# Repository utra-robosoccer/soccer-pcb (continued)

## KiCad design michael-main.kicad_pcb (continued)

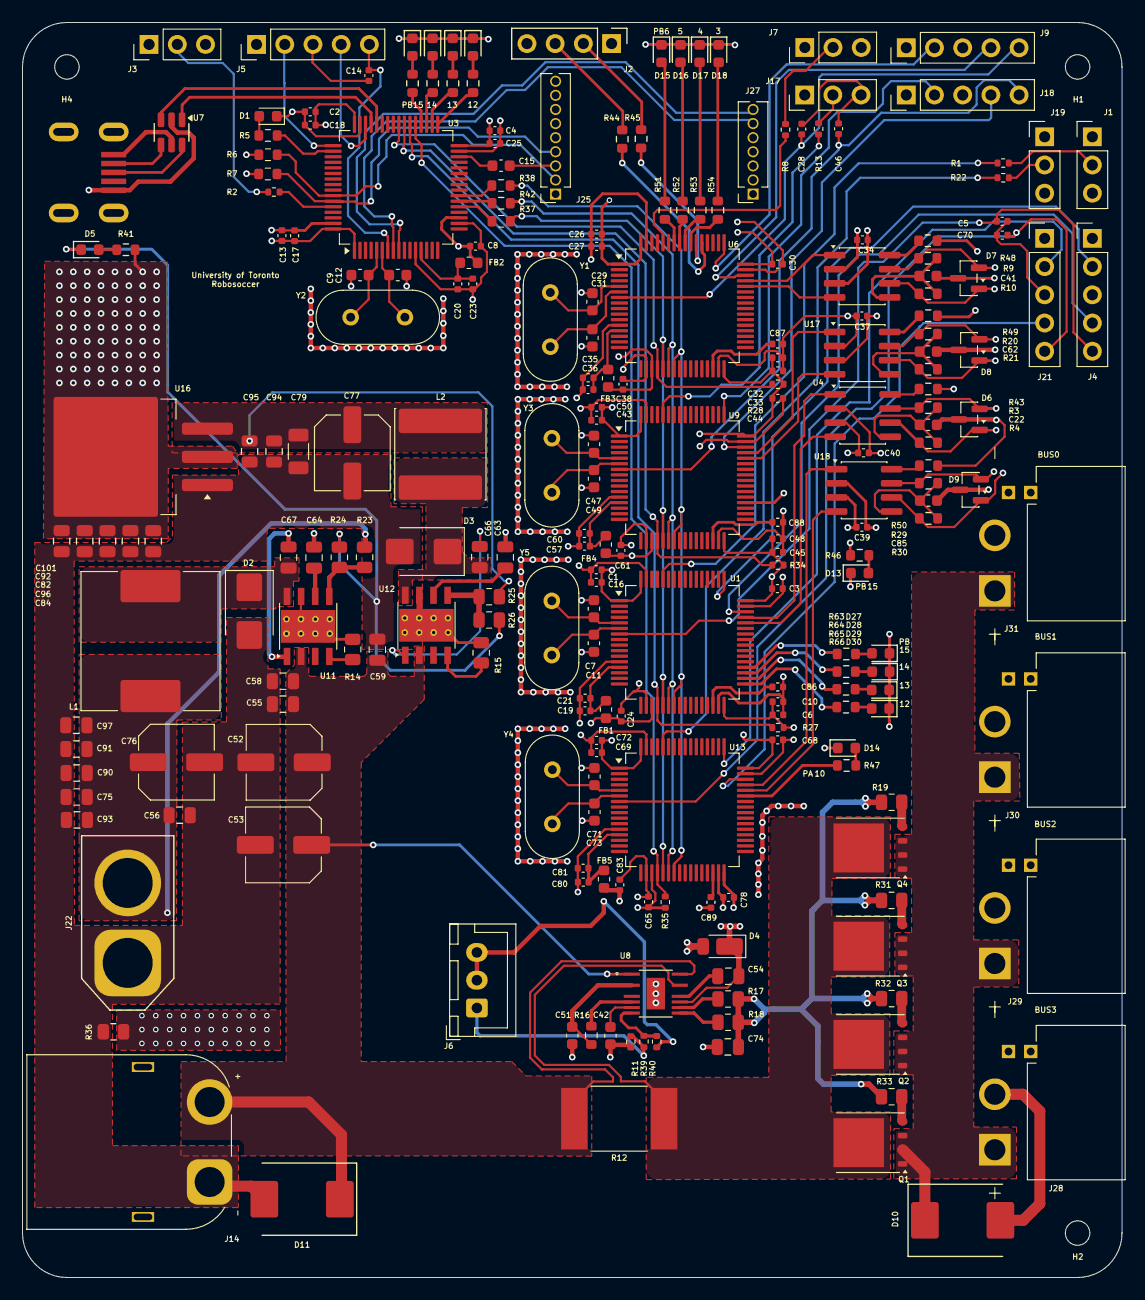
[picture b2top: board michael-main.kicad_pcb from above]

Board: 4 copper layers, 99.0 x 113.0 mm, 239 parts (0 on the bottom side), 154 nets.

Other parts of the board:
R40: 0; R_0402_1005Metric

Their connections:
+3.3V: R40.1; also elsewhere on the board
unnamed 130: R40.2; also elsewhere on the board

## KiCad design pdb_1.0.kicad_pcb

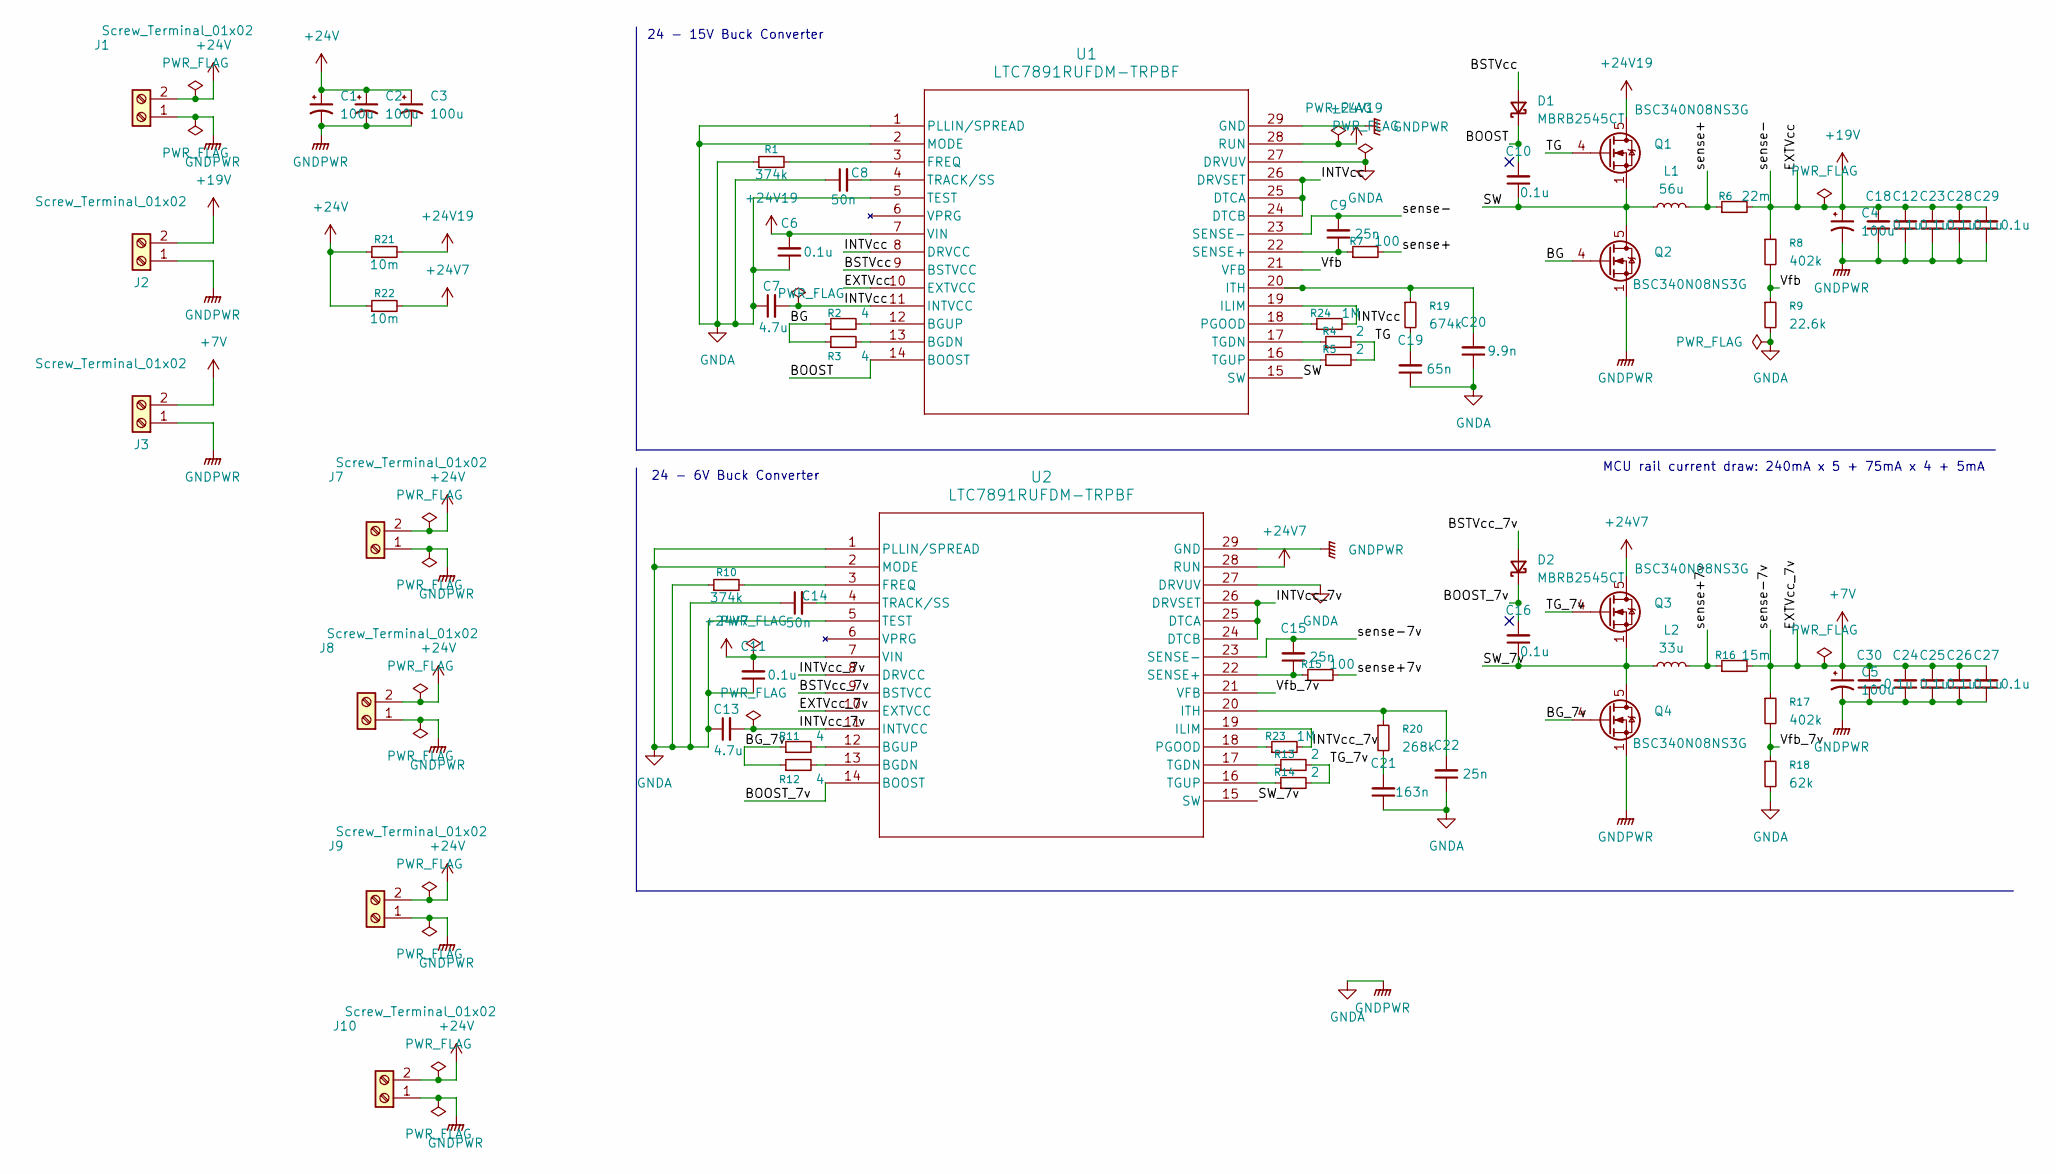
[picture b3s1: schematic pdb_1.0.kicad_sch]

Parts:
C1, C2, C3, C4, C5: 100u; C_Elec_10x10.2
C6, C11: 0.1u; C_0805_2012Metric_Pad1.18x1.45mm_HandSolder
C7, C13: 4.7u; C_0805_2012Metric
C8, C14: 50n; C_0805_2012Metric
C9, C15, C22: 25n; C_0805_2012Metric
C10, C16: 0.1u; C_0805_2012Metric
C12, C23, C24, C25, C26, C27, C28, C29: 0.1u; C_1206_3216Metric
C18, C30: 0.1u; CP_Elec_5x5.4
C19: 65n; C_0805_2012Metric_Pad1.18x1.45mm_HandSolder
C20: 9.9n; C_0805_2012Metric_Pad1.18x1.45mm_HandSolder
C21: 163n; C_0805_2012Metric
D1, D2: MBRB2545CT; TO-263-3_TabPin2
J1, J7, J8, J9, J10: Screw_Terminal_01x02; AMASS_XT90PW-M_1x02_P10.90mm_Horizontal
J2: Screw_Terminal_01x02; AMASS_XT60PW-M_1x02_P7.20mm_Horizontal
J3: Screw_Terminal_01x02; AMASS_XT30PW-M_1x02_P2.50mm_Horizontal
L1: 56u; L_Wuerth_HCI-2212
L2: 33u; L_Wuerth_HCI-1890
Q1, Q2, Q3, Q4: BSC340N08NS3G; TDSON-8-1
R1: 374k; R_0805_2012Metric
R2, R3, R11, R12: 4; C_0805_2012Metric
R4, R5, R13, R14: 2; C_0805_2012Metric
R6: 22m; R_1210_3225Metric
R7, R15: 100; C_0805_2012Metric
R8, R17: 402k; R_0805_2012Metric
R9: 22.6k; R_0805_2012Metric
R10: 374k; C_0805_2012Metric
R16: 15m; R_1210_3225Metric
R18: 62k; R_0805_2012Metric
R19: 674k; C_0805_2012Metric_Pad1.18x1.45mm_HandSolder
R20: 268k; C_0805_2012Metric
R21, R22: 10m; R_3425Metric
R23, R24: 1M; C_0805_2012Metric
U1, U2: LTC7891RUFDM-TRPBF; 05-08-1682_ADI

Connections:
+7V: C5.1, C15.2, C24.2, C25.2, C26.2, C27.2, C30.2, J3.2, R16.2, R17.1, U2.10 (EXTVCC), U2.23 (SENSE-); also elsewhere on the board
+19V: C4.1, C9.2, C12.2, C18.2, C23.2, C28.2, C29.2, J2.2, R6.2, R8.1, U1.10 (EXTVCC), U1.23 (SENSE-)
+24V: C1.1, C2.1, C3.1, J1.2, J7.2, J8.2, J9.2, J10.2, R21.1, R22.1
+24V7: C11.2, Q3.5 (D), R22.2, U2.7 (VIN), U2.28 (RUN)
+24V19: C6.2, Q1.5 (D), R21.2, U1.7 (VIN), U1.28 (RUN)
/BG: Q2.4 (G), R2.1, R3.1
/BG_7v: Q4.4 (G), R11.1, R12.1
/BOOST: C10.2, D1.1 (K), U1.14 (BOOST)
/BOOST_7v: C16.2, D2.1 (K), U2.14 (BOOST)
/BSTVcc: D1.2 (A), U1.9 (BSTVCC)
/BSTVcc_7v: D2.2 (A), U2.9 (BSTVCC)
/INTVcc: C7.2, R24.2, U1.8 (DRVCC), U1.11 (INTVCC), U1.19 (ILIM), U1.24 (DTCB), U1.25 (DTCA), U1.26 (DRVSET)
/INTVcc_7v: C13.2, R23.2, U2.8 (DRVCC), U2.11 (INTVCC), U2.19 (ILIM), U2.24 (DTCB), U2.25 (DTCA), U2.26 (DRVSET)
/SW: C10.1, L1.1, Q1.1 (S), Q1.2 (S), Q1.3 (S), Q2.5 (D), U1.15 (SW)
/SW_7v: C16.1, L2.1, Q3.1 (S), Q3.2 (S), Q3.3 (S), Q4.5 (D), U2.15 (SW)
/TG: Q1.4 (G), R4.2, R5.2
/TG_7v: Q3.4 (G), R13.2, R14.2
/Vfb: R8.2, R9.1, U1.21 (VFB)
/Vfb_7v: R17.2, R18.1, U2.21 (VFB)
/sense+: L1.2, R6.1, R7.2
/sense+7v: L2.2, R15.2, R16.1
GNDA: C1.2, C2.2, C3.2, C4.2, C5.2, C6.1, C7.1, C8.1, C11.1, C12.1, C13.1, C14.1, C18.1, C19.1, C20.1, C21.1, C22.1, C23.1, C24.1, C25.1, C26.1, C27.1, C28.1, C29.1, C30.1, J1.1, J2.1, J3.1, J7.1, J8.1, J9.1, J10.1, Q2.1 (S), Q2.2 (S), Q2.3 (S), Q4.1 (S), Q4.2 (S), Q4.3 (S), R1.1, R9.2, R10.1, R18.2, U1.1 (PLLIN/SPREAD), U1.2 (MODE), U1.5 (TEST), U1.27 (DRVUV), U1.29 (GND), U2.1 (PLLIN/SPREAD), U2.2 (MODE), U2.5 (TEST), U2.27 (DRVUV), U2.29 (GND)
unnamed: C19.2, R19.2
unnamed: C21.2, R20.2
unnamed: R3.2, U1.13 (BGDN)
unnamed: R2.2, U1.12 (BGUP)
unnamed: R1.2, U1.3 (FREQ)
unnamed: C20.2, R19.1, U1.20 (ITH)
unnamed: R24.1, U1.18 (PGOOD)
unnamed: C9.1, R7.1, U1.22 (SENSE+)
unnamed: R4.1, U1.17 (TGDN)
unnamed: R5.1, U1.16 (TGUP)
unnamed: C8.2, U1.4 (TRACK/SS)
unnamed: R12.2, U2.13 (BGDN)
unnamed: R11.2, U2.12 (BGUP)
unnamed: R10.2, U2.3 (FREQ)
unnamed: C22.2, R20.1, U2.20 (ITH)
unnamed: R23.1, U2.18 (PGOOD)
unnamed: C15.1, R15.1, U2.22 (SENSE+)
unnamed: R13.1, U2.17 (TGDN)
unnamed: R14.1, U2.16 (TGUP)
unnamed: C14.2, U2.4 (TRACK/SS)

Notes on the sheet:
24 - 6V Buck Converter
MCU rail current draw: 240mA x 5 + 75mA x 4 + 5mA
24 - 15V Buck Converter

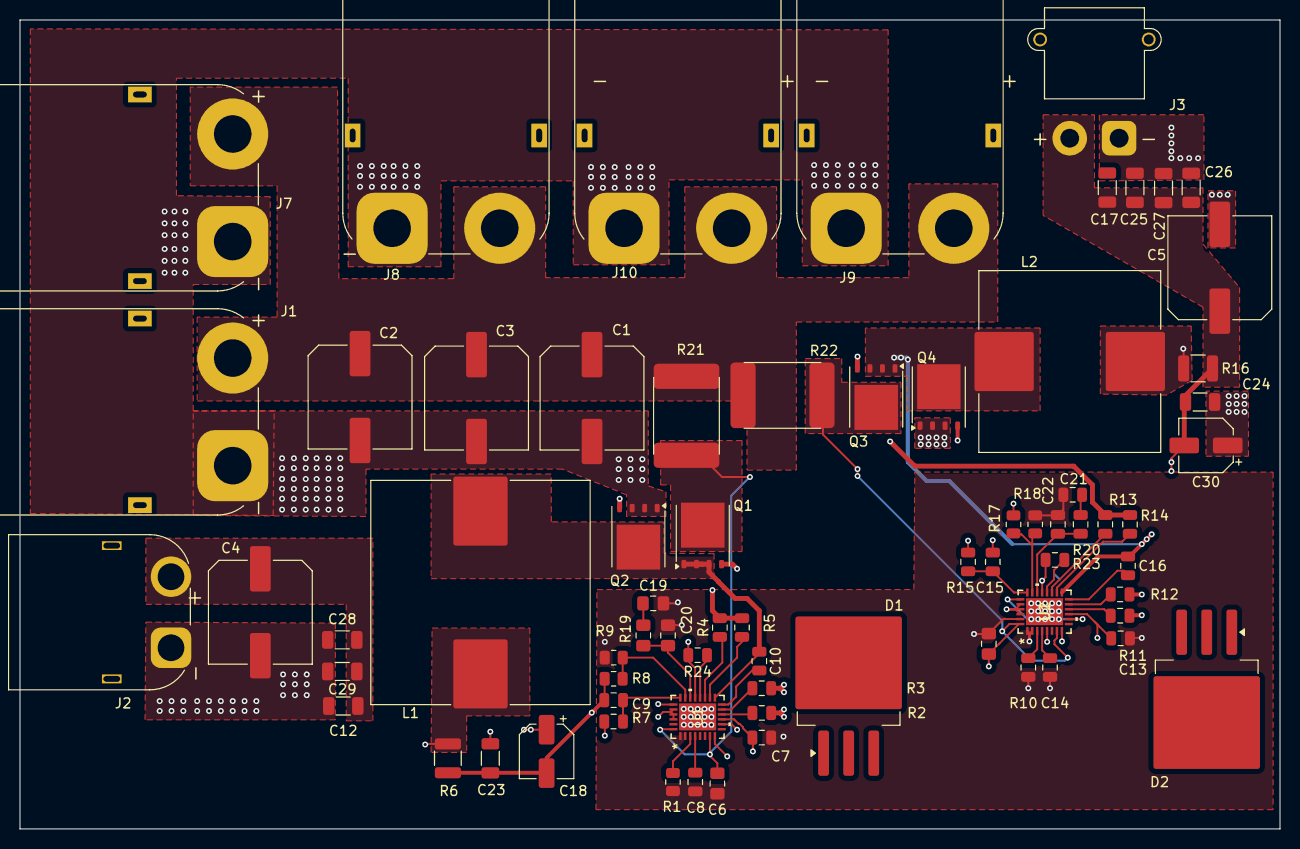
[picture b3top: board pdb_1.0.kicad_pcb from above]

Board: 4 copper layers, 127.7 x 81.9 mm, 71 parts (0 on the bottom side), 42 nets.

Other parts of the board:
C17: 0.1u; C_1206_3216Metric

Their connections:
+7V: C17.2; also elsewhere on the board

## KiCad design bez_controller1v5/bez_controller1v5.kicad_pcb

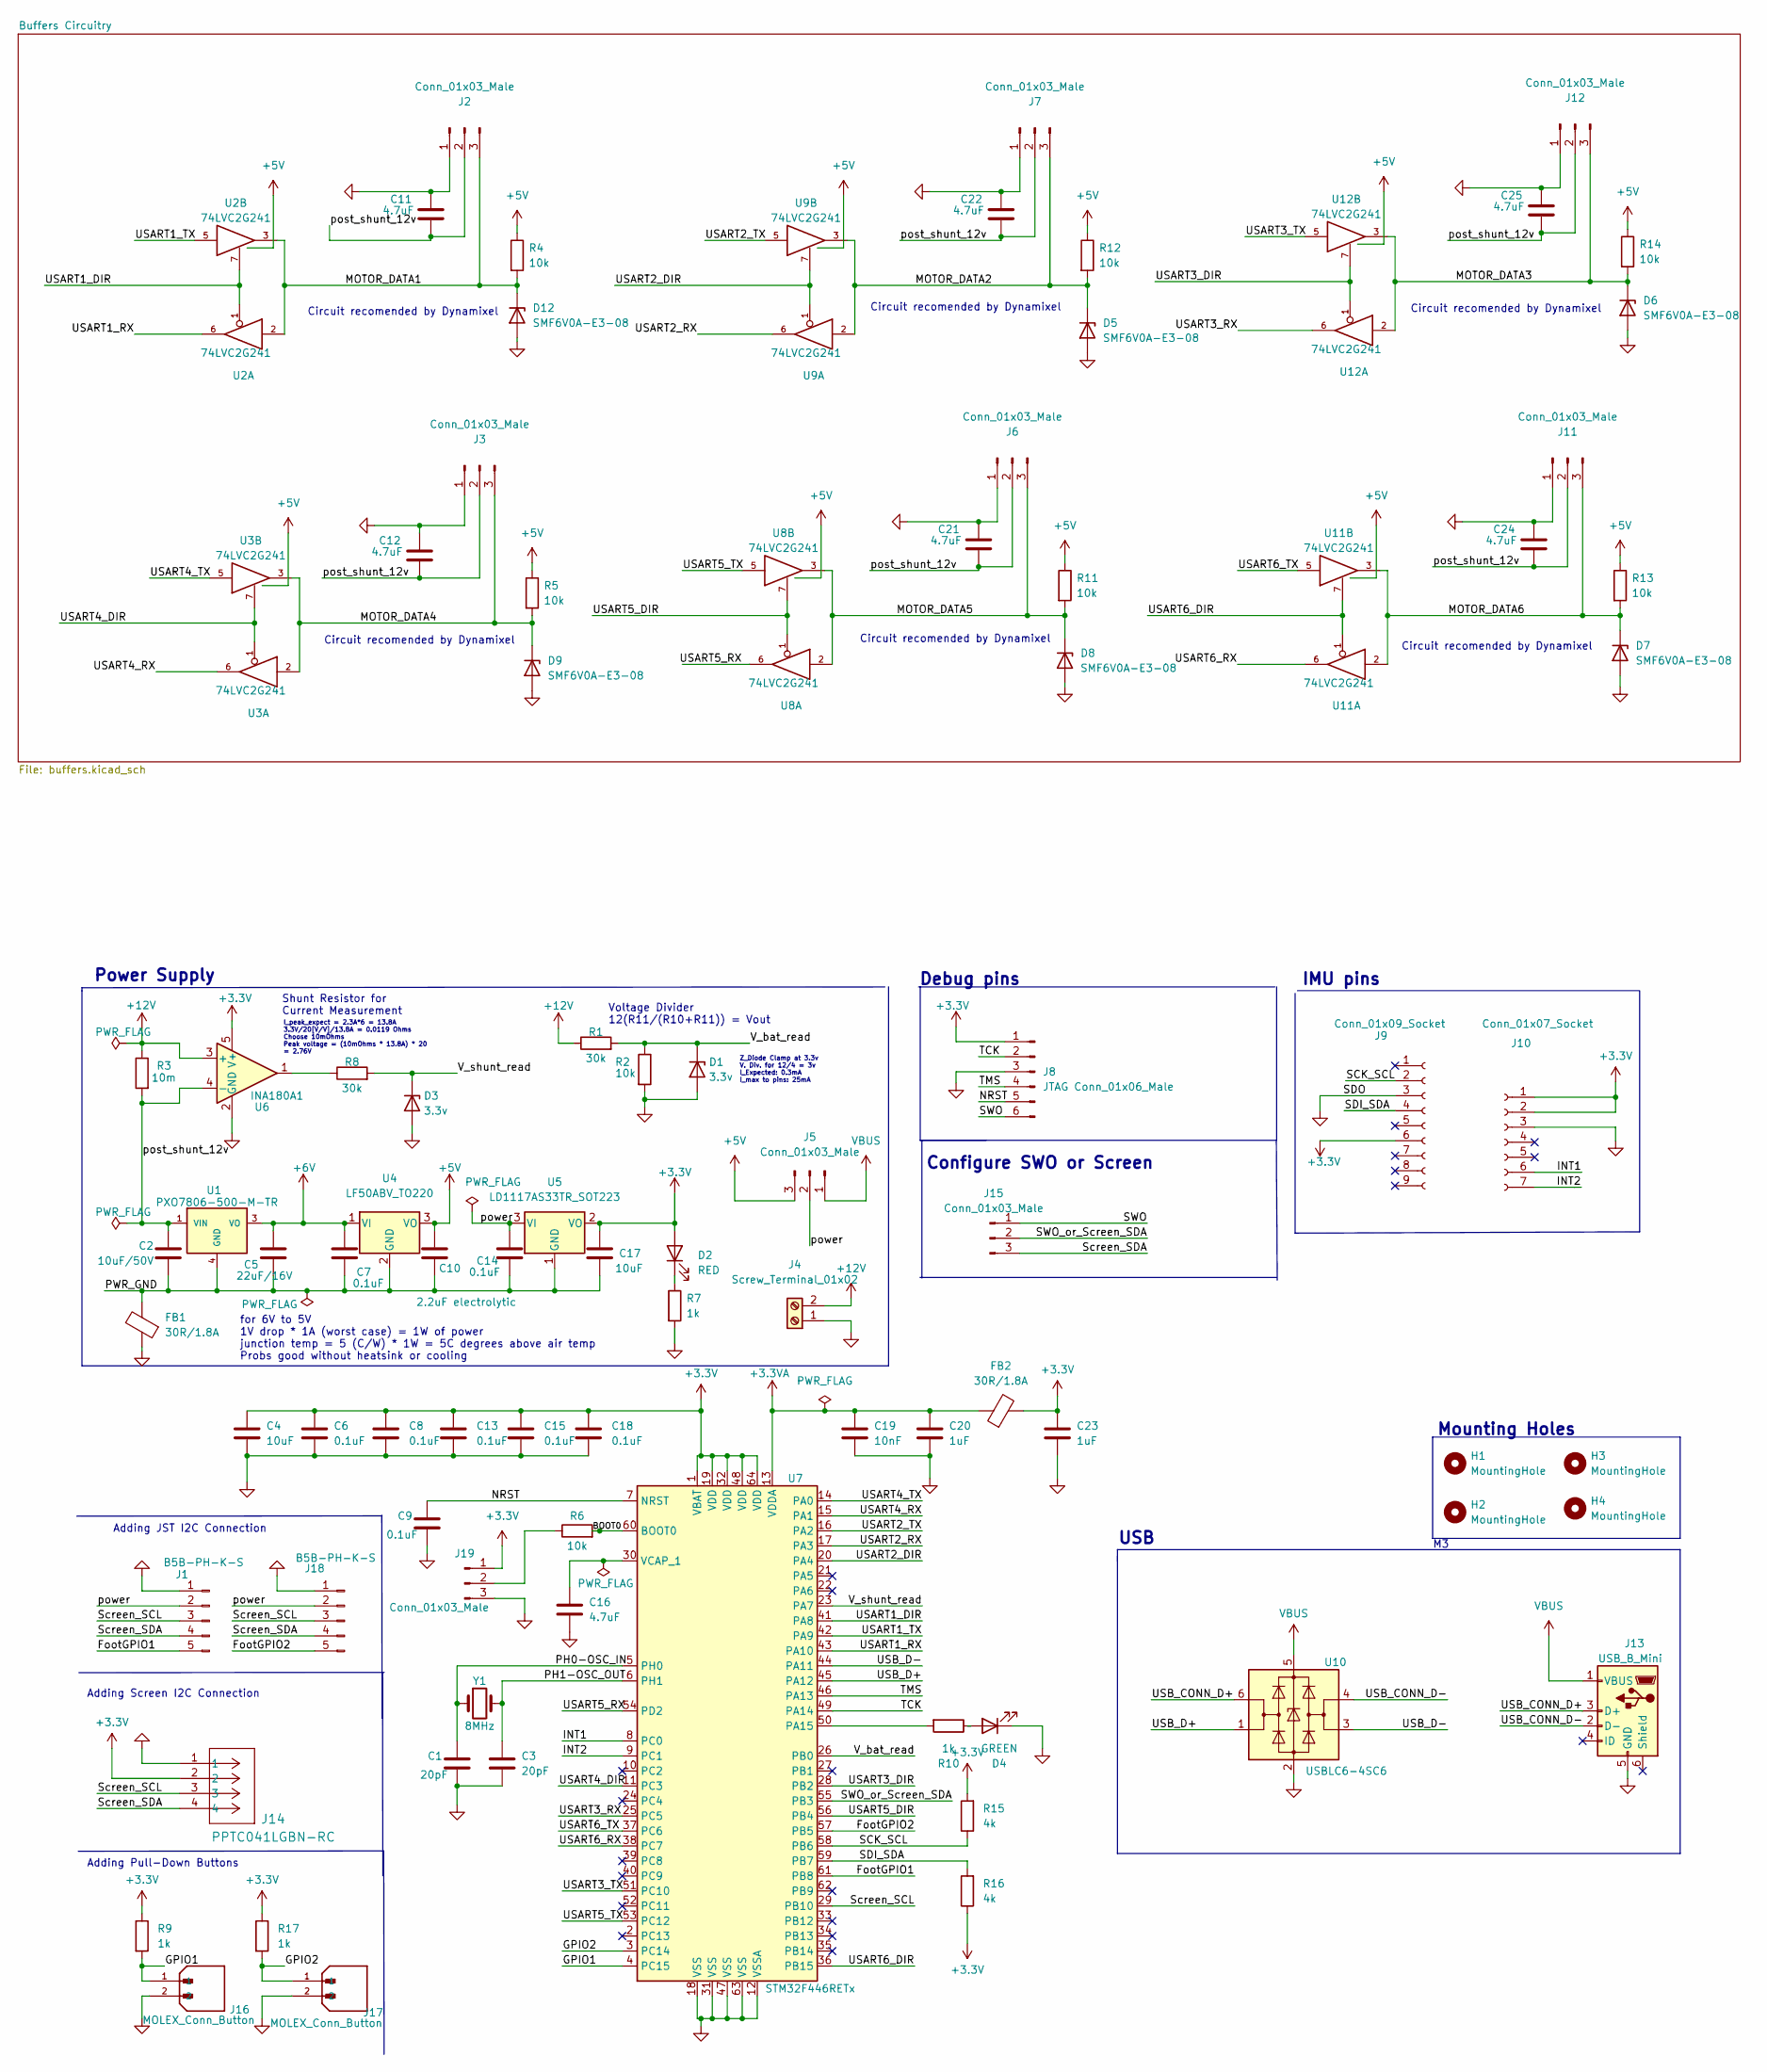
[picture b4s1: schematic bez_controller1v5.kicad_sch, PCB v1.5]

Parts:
C1, C3: 20pF; C_0603_1608Metric
C2: 10uF/50V; C_0805_2012Metric
C4, C17: 10uF; C_0603_1608Metric
C5: 22uF/16V; C_0805_2012Metric
C6, C7, C8, C9, C13, C14, C15, C18: 0.1uF; C_0603_1608Metric
C10: 2.2uF electrolytic; C_0603_1608Metric
C11, C12, C16, C21, C22, C24, C25: 4.7uF; C_0603_1608Metric
C19: 10nF; C_0603_1608Metric
C20, C23: 1uF; C_0603_1608Metric
D1, D3: 3.3v; D_0603_1608Metric
D2: RED; LED_0603_1608Metric
D4: GREEN; LED_0603_1608Metric
D5, D6, D7, D8, D9, D12: SMF6V0A-E3-08; D_SMF
FB1, FB2: 30R/1.8A; L_0603_1608Metric
H1, H2, H3, H4: MountingHole; MountingHole_3.2mm_M3
J1, J18: B5B-PH-K-S; JST_PH_B5B-PH-K_1x05_P2.00mm_Vertical
J2, J3, J6, J7, J11, J12: Conn_01x03_Male; CONN_S3B-XH-ALFSN_JST
J4: Screw_Terminal_01x02; AMASS_XT60PW-M_1x02_P7.20mm_Horizontal
J5, J15, J19: Conn_01x03_Male; PinHeader_1x03_P2.54mm_Vertical
J8: JTAG Conn_01x06_Male; PinHeader_1x06_P2.54mm_Vertical
J9: Conn_01x09_Socket; PinSocket_1x09_P1.27mm_Vertical
J10: Conn_01x07_Socket; PinSocket_1x07_P1.27mm_Vertical
J13: USB_B_Mini; USB_MINI
J14: PPTC041LGBN-RC; CONN_PPTC041LGBN-RC_SUL
J16, J17: MOLEX_Conn_Button; CON_530480210_MOL; PARTREV A
R1, R8: 30k; R_0603_1608Metric
R2, R4, R5, R6, R11, R12, R13, R14: 10k; R_0603_1608Metric
R3: 10m; R_2010_5025Metric
R7, R9, R10, R17: 1k; R_0603_1608Metric
R15, R16: 4k; R_0603_1608Metric
U1: CONV_PXO7806-500-M-TR
U2, U3, U8, U9, U11, U12: 74LVC2G241; VSSOP-8_3.0x3.0mm_P0.65mm
U4: LF50ABV_TO220; TO-220-3_Vertical
U5: LD1117AS33TR_SOT223; SOT-223-3_TabPin2
U6: INA180A1; SOT-23-5
U7: STM32F446RETx; LQFP-64_10x10mm_P0.5mm
U10: USBLC6-4SC6; SOT-23-6
Y1: 8MHz; Crystal_HC49-U_Vertical

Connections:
+3.3V: C4.1, C6.1, C8.1, C13.1, C15.1, C17.1, C18.1, C23.1, D2.2 (A), FB2.2, J8.1, J9.6, J10.1, J10.2, J14.2, J19.1, R9.1, R15.2, R16.1, R17.1, U5.2 (VO), U6.5 (V+), U7.1 (VBAT), U7.19 (VDD), U7.32 (VDD), U7.48 (VDD), U7.64 (VDD)
+3.3VA: C19.1, C20.1, FB2.1, U7.13 (VDDA)
+5V: C10.1, J5.3, R4.1, R5.1, R11.1, R12.1, R13.1, R14.1, U2.8 (VCC), U3.8 (VCC), U4.3 (VO), U8.8 (VCC), U9.8 (VCC), U11.8 (VCC), U12.8 (VCC)
+6V: C5.1, C7.1, U1.3 (VO), U4.1 (VI)
+12V: J4.2, R1.1, R3.1, U6.3 (+)
/BOOT0: R6.2, U7.60 (BOOT0)
/FootGPIO1: J1.5, U7.61 (PB8)
/FootGPIO2: J18.5, U7.57 (PB5)
/GPIO1: J16.1, R9.2, U7.4 (PC15)
/GPIO2: J17.1, R17.2, U7.3 (PC14)
/INT1: J10.6, U7.8 (PC0)
/INT2: J10.7, U7.9 (PC1)
/MOTOR_DATA1: D12.1 (K), J2.3, R4.2, U2.2, U2.3
/MOTOR_DATA2: D5.1 (K), J7.3, R12.2, U9.2, U9.3
/MOTOR_DATA3: D6.1 (K), J12.3, R14.2, U12.2, U12.3
/MOTOR_DATA4: D9.1 (K), J3.3, R5.2, U3.2, U3.3
/MOTOR_DATA5: D8.1 (K), J6.3, R11.2, U8.2, U8.3
/MOTOR_DATA6: D7.1 (K), J11.3, R13.2, U11.2, U11.3
/NRST: C9.1, J8.5, U7.7 (NRST)
/PH0-OSC_IN: C1.1, U7.5 (PH0), Y1.1
/PH1-OSC_OUT: C3.1, U7.6 (PH1), Y1.2
/PWR_GND: C2.2, C5.2, C7.2, C10.2, C14.2, C17.2, FB1.2, U1.4 (GND), U4.2 (GND), U5.1 (GND)
/SCK_SCL: J9.2, R15.1, U7.58 (PB6)
/SDI_SDA: J9.4, R16.2, U7.59 (PB7)
/SWO: J8.6, J15.1
/SWO_or_Screen_SDA: J15.2, U7.55 (PB3)
/Screen_SCL: J1.3, J14.3, J18.3, U7.29 (PB10)
/Screen_SDA: J1.4, J14.4, J15.3, J18.4
/TCK: J8.2, U7.49 (PA14)
/TMS: J8.4, U7.46 (PA13)
/USART1_DIR: U2.1, U2.7, U7.41 (PA8)
/USART1_RX: U2.6, U7.43 (PA10)
/USART1_TX: U2.5, U7.42 (PA9)
/USART2_DIR: U7.20 (PA4), U9.1, U9.7
/USART2_RX: U7.17 (PA3), U9.6
/USART2_TX: U7.16 (PA2), U9.5
/USART3_DIR: U7.28 (PB2), U12.1, U12.7
/USART3_RX: U7.25 (PC5), U12.6
/USART3_TX: U7.51 (PC10), U12.5
/USART4_DIR: U3.1, U3.7, U7.11 (PC3)
/USART4_RX: U3.6, U7.15 (PA1)
/USART4_TX: U3.5, U7.14 (PA0)
/USART5_DIR: U7.56 (PB4), U8.1, U8.7
/USART5_RX: U7.54 (PD2), U8.6
/USART5_TX: U7.53 (PC12), U8.5
/USART6_DIR: U7.36 (PB15), U11.1, U11.7
/USART6_RX: U7.38 (PC7), U11.6
/USART6_TX: U7.37 (PC6), U11.5
/USB_CONN_D+: J13.3 (D+), U10.6 (I/O1)
/USB_CONN_D-: J13.2 (D-), U10.4 (I/O2)
/USB_D+: U7.45 (PA12), U10.1 (I/O1)
/USB_D-: U7.44 (PA11), U10.3 (I/O2)
/V_bat_read: D1.1 (K), R1.2, R2.1, U7.26 (PB0)
/V_shunt_read: D3.1 (K), R8.2, U7.23 (PA7)
/post_shunt_12v: C2.1, C11.2, C12.2, C21.2, C22.2, C24.2, C25.2, J2.2, J3.2, J6.2, J7.2, J11.2, J12.2, R3.2, U1.1 (VIN), U6.4 (-)
/power: C14.1, J1.2, J5.2, J18.2, U5.3 (VI)
GND: C1.2, C3.2, C4.2, C6.2, C8.2, C9.2, C11.1, C12.1, C13.2, C15.2, C16.2, C18.2, C19.2, C20.2, C21.1, C22.1, C23.2, C24.1, C25.1, D1.2 (A), D3.2 (A), D4.1 (K), D5.2 (A), D6.2 (A), D7.2 (A), D8.2 (A), D9.2 (A), D12.2 (A), FB1.1, J1.1, J2.1, J3.1, J4.1, J6.1, J7.1, J8.3, J9.3, J10.3, J11.1, J12.1, J13.5 (GND), J14.1, J16.2, J17.2, J18.1, J19.3, R2.2, R7.2, U2.4 (GND), U3.4 (GND), U6.2 (GND), U7.12 (VSSA), U7.18 (VSS), U7.31 (VSS), U7.47 (VSS), U7.63 (VSS), U8.4 (GND), U9.4 (GND), U10.2 (GND), U11.4 (GND), U12.4 (GND)
unnamed: D2.1 (K), R7.1
unnamed: D4.2 (A), R10.1
unnamed: J19.2, R6.1
unnamed: R8.1, U6.1
unnamed: R10.2, U7.50 (PA15)
unnamed: C16.1, U7.30 (VCAP_1)
VBUS: J5.1, J13.1 (VBUS), U10.5 (VBUS)

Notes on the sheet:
IMU pins
Adding JST I2C Connection
USB
Configure SWO or Screen
Circuit recomended by Dynamixel
I_peak_expect = 2.3A*6 = 13.8A 3.3V/20[V/V]/13.8A = 0.0119 Ohms Choose 10mOhms Peak voltage = (10mOhms * 13.8A) * 20 = 2.76V
Debug pins
Mounting Holes
Z_Diode Clamp at 3.3v V. Div. for 12/4 = 3v I_Expected: 0.3mA I_max to pins: 25mA
Power Supply
Voltage Divider 12(R11/(R10+R11)) = Vout
Shunt Resistor for Current Measurement
Adding Pull-Down Buttons
for 6V to 5V 1V drop * 1A (worst case) = 1W of power junction temp = 5 (C/W) * 1W = 5C degrees above air temp Probs good without heatsink or cooling
Adding Screen I2C Connection

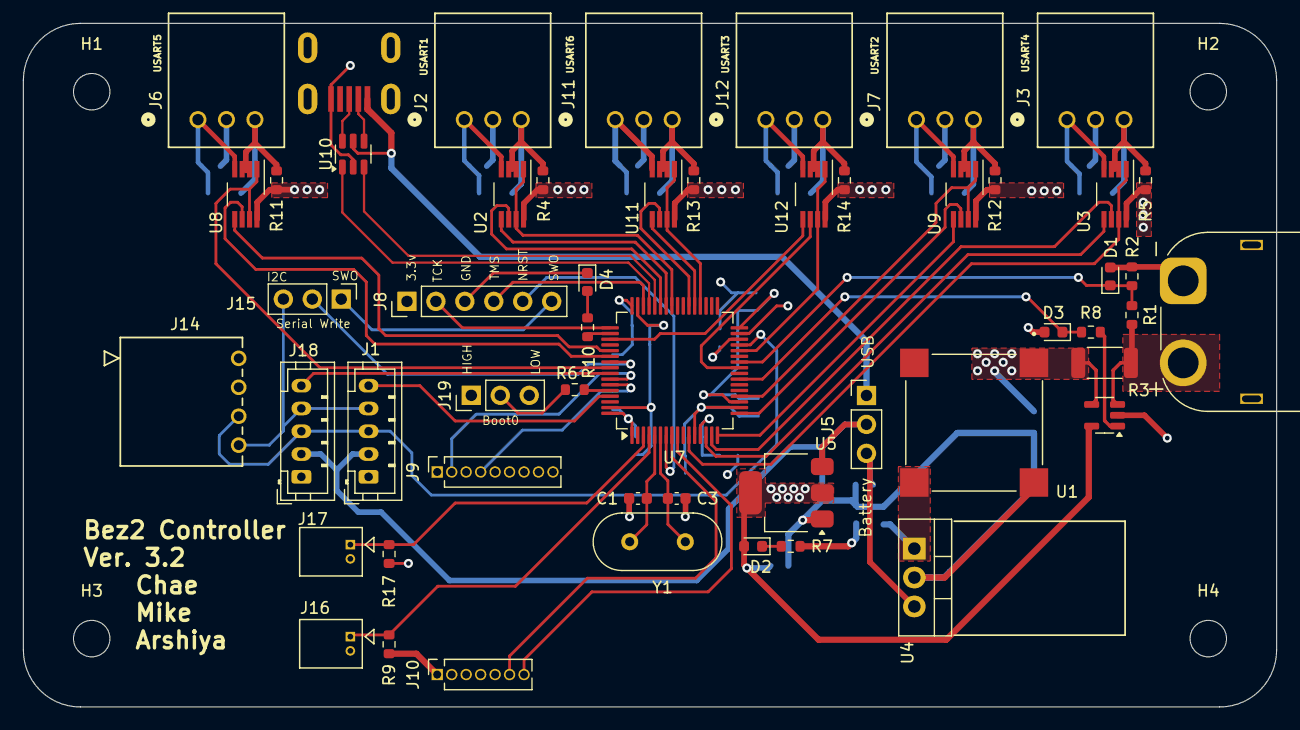
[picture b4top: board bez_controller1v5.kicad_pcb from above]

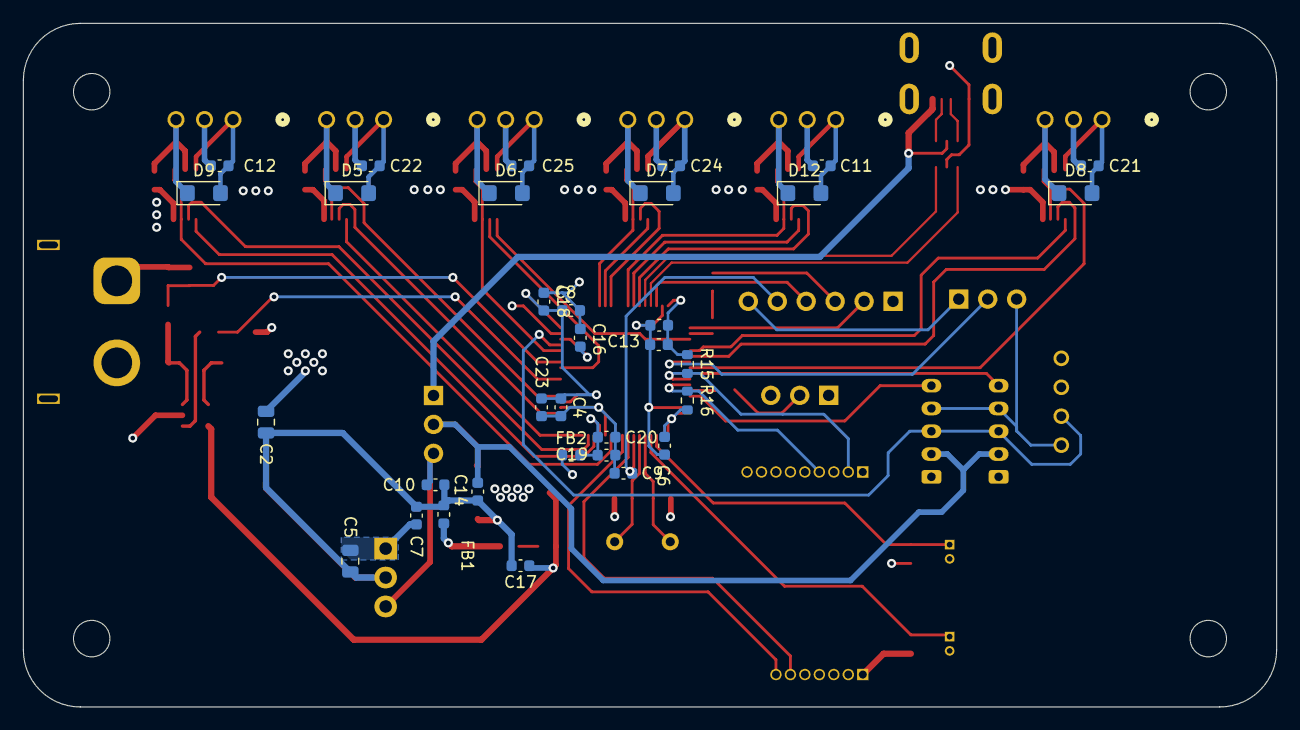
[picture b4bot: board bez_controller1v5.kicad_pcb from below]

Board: 4 copper layers, 110.0 x 60.0 mm, 90 parts (33 on the bottom side), 64 nets.

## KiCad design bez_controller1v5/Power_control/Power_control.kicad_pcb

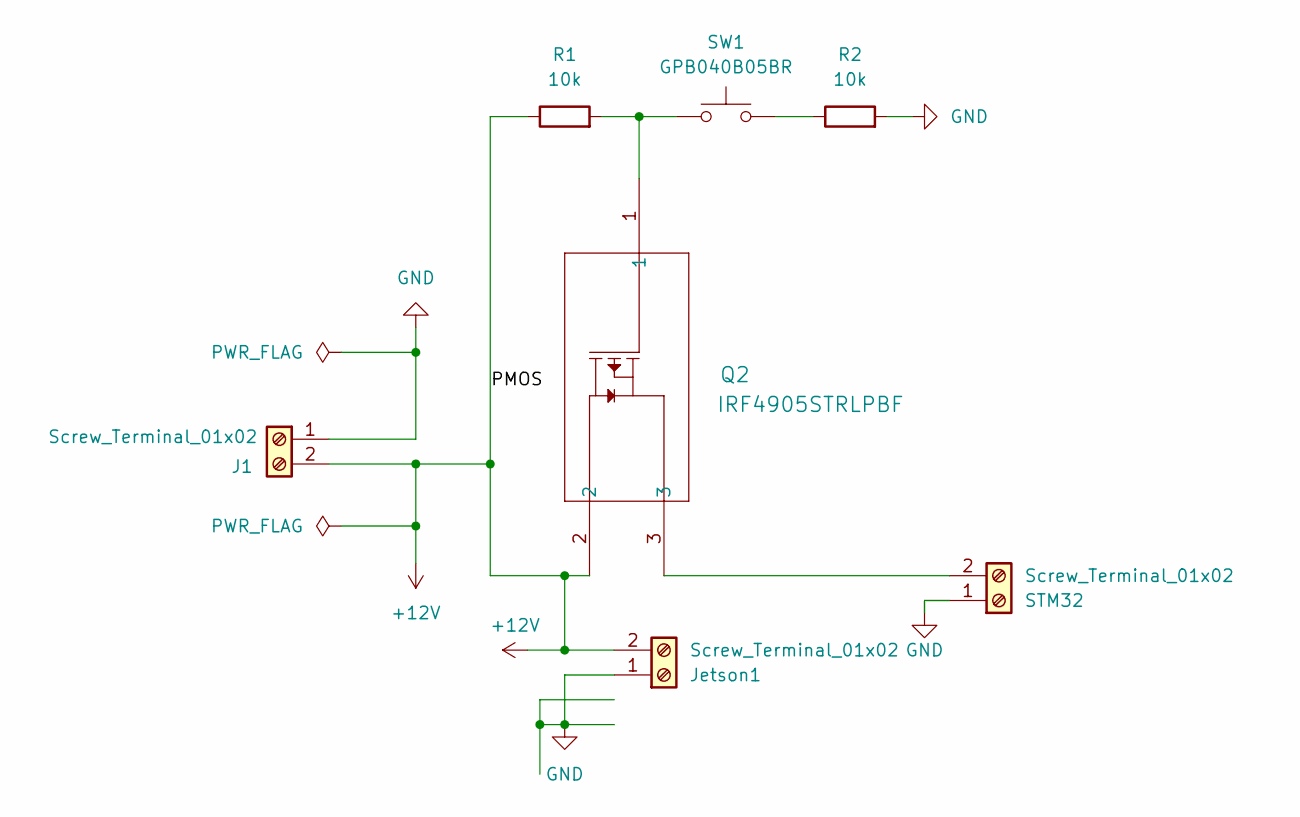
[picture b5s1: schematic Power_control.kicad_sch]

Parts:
J1: Screw_Terminal_01x02; AMASS_XT60-M
Jetson1: Screw_Terminal_01x02; AMASS_XT60PW-F_1x02_P7.20mm_Horizontal
Q2: IRF4905STRLPBF; IRF4905
R1, R2: 10k; R_0603_1608Metric
STM32: Screw_Terminal_01x02; AMASS_XT60PW-F_1x02_P7.20mm_Horizontal
SW1: GPB040B05BR

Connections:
+12V: J1.2, Jetson1.2, Q2.2, R1.1
GND: J1.1, Jetson1.1, R2.2, STM32.1
unnamed: Q2.1, R1.2, SW1.1
unnamed: R2.1, SW1.2
unnamed: Q2.3, STM32.2

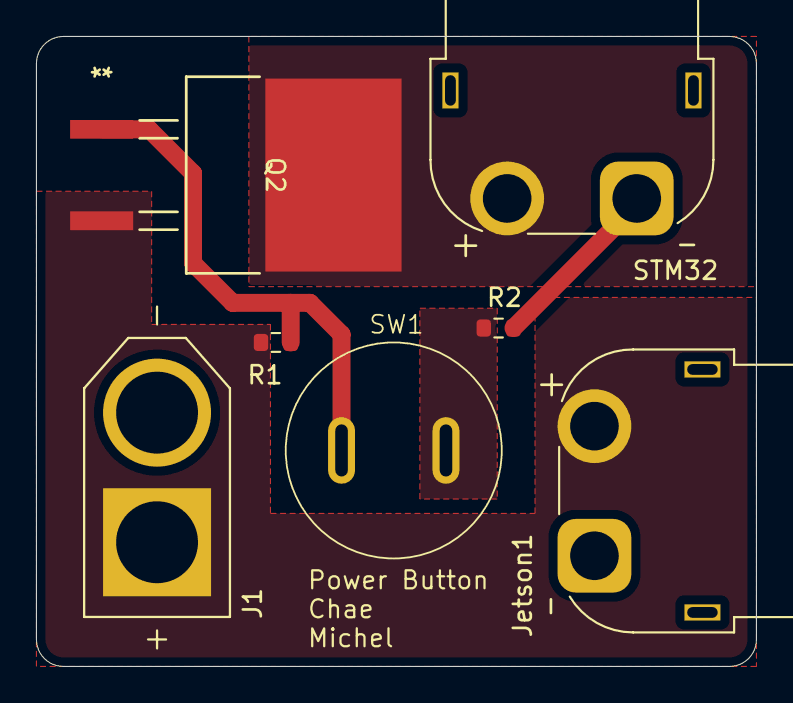
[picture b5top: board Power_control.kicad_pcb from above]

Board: 2 copper layers, 40.0 x 35.0 mm, 7 parts (0 on the bottom side), 5 nets.

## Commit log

2018-02-25 First Controller Board
2018-02-25 AX-12 circuit
2018-02-25 Library added, Dip switch and power monitoring header was added
2018-03-05 final pcb iter. 1
2018-03-05 Dimensions Added
2018-05-14 remaining changes
2018-08-09 Added breakout board files
    Breakout boards for 3 different chips
2018-10-12 Update Breakout board files/eagle.epf
    Added in project file for breakout board
2018-10-13 Breakout Board Solutions
2018-10-13 Added stuff for breakout board for STM32F767
    Pin infos, pin picture, schematic
2018-10-18 Moved breakout board to new directory and added pin excel file
2018-11-04 Components added to breakout board
    Parts from the STM32F446RE_subcircuit (e.g. oscillators) added to the breakout board. Also added pin headers for ethernet.
2018-11-08 First draft of breakout board complete
    Pin excel file also updated. For the schematic, added functionality from previous board, connections for ethernet and JTAG, and also exposed all of the other IO pins
2019-01-13 PCB almost done - impedance matching on diff pair remaining
2019-01-13 step down convertor PCB.
2019-01-16 Revised ethernet connections
2019-02-05 Ethernet PCB finalized
2019-02-06 Updated Ethernet Connection part
2019-02-28 Incorporated small changes
    As per February 9 2019 Slack message in the electrical channel.
    1- connect the 3V3 of Ethernet breakout board to VDD
    2- the 12v input should be provided in two ways: regular pin header / phoenix jack (already there)
    3- Pull down the BOOT0 pin 10k ohm
    4- Hook up LEDs to these pins on the microcontroller:
    PD15(pin 62) - PD7(pin 88) - PD14(pin 61)
2019-03-23 Pre-design schematic done
    Incorporated changes discussed in March 21 meeting
2019-03-23 Iniitial Progress on designing PCB
    Organized the components onto the design space. Put the pairing capacitors near the VCC and VSS pins as suggested in meeting.
2019-03-24 Organized components in the .brd file
    Still have to route it
2019-03-30 Mar 26 Feedback incorporated
    Verification for correct 100nF cap package required. As per crystal datasheet, traces from crystal to microcontroller were minimized.
2019-04-05 Apr 2 Feedback incorporated
    Please check if the surface mount of resistors, caps, and LEDs are ok. Also, I noticed there's a lot of free space.
2019-04-06 Incorporated April 6 Comments
2019-04-14 Added Schematic by Luis - Apr 14
2019-04-19 Current routing progress
    Routed most of top breakout pins
2019-04-19 xmega a3u header pcb added
2019-04-21 Replacement
    Rotated the microcontroller. Will route the side pins later.
2019-04-24 Ethernet and Crystal Rounting
    First draft of ethernet and crystal routing. If ok, then will move on to sid epin headers
2019-04-28 First try at routing everything
    Currently it's a mess, so will redo most of the routing. But this is the current progress
2019-05-01 First complete routing
2019-05-02 May 1 Feedback Incorporated
    Fixed the irregularity and added more space between traces and the pads
2019-05-03 May 1 part 2
2019-05-03 May 2 part 2
    Cap connection changed
    Same length applied
2019-05-03 part 3
2019-05-03 part x
2019-05-14 polygon added
2022-05-09 NUCLEO_F446 breakout started
2022-05-09 test hook
2022-05-09 clean up test
2022-06-22 [ImgBot] Optimize images
    *Total -- 18.24kb -> 6.47kb (64.54%)
    /STM32F767VG_breakout/even newer ethernet connections to breakout.png -- 9.25kb -> 3.00kb (67.55%)
    /STM32F767VG_breakout/old ethernet connections to breakout.png -- 9.00kb -> 3.47kb (61.45%)
2023-03-01 current files
2023-03-05 added buffers and IMU wiring + something else I forget
2023-03-08 add backup .zip
2023-03-08 use 1k pullup on data lines and 1k for LEDs
2023-03-11 add smps and caps
2023-03-11 add voltage divider
2023-03-13 forgot the uart dir pins
2023-03-16 footprings assigned
2023-03-20 rough layout
2023-03-22 placement of components might be done, need to double check footprints, schematic
2023-03-23 uart4 fixed, board cutout, fix layout, signal routing done except for buffers
2023-03-24 finished routing signals
2023-03-24 get rid of backups
2023-03-29 all signals and power done, need to deal with errors now
2023-05-01 fixed errors, added labels, custom usb footprint
2023-05-01 sign name and add logo
2023-05-01 update signature, add labels for imu pins
2023-06-06 selected wrong usb protection
2023-11-16 Added a means of measuring battery voltage and current + circuit protection
2024-01-06 new rounted PCB
2024-01-06 new route PCB
2024-01-16 Added connection for Voltage Measurement and Current Measurement, also cleaned up PCB a little more
2024-01-17 fixing some routing and components footprint
2024-01-20 change footprint of shunt R and electrolytic C
2024-01-27 added USB footprint
2024-01-27 fix imu footprint, adjust traces for 12V, change capacitor footprint
2024-01-27 add headers for GPIO/buttons
2024-02-03 routed IMU pins and minor changes
2024-02-03 Shorted grounds together
2024-02-03 Rounded edges
2024-02-03 Straightened some more lines
2024-02-16 added label for pins, changed USB and C10 footprint
2024-02-24 Add SPI lines for IMU
2024-02-24 connected SPI
2024-02-27 final change
2024-02-29 fix labels, make labels bigger, add +12V -GND symbol
2024-02-29 flip motor connectors to right orientation
2024-02-29 use xt60 power connector
2024-02-29 remove warnings, clean up labels, redo some wiring
2024-03-02 remove spi wires from schematic
2024-03-02 new connection for SDA and SCL
2024-03-02 add interrupt pins + cleanup
2024-03-02 motor cleanup
2024-03-09 Go over PCB final time, check connections, imu distance, power, shunt
2024-03-16 add manufacturing files
2024-03-16 modify bom and pos file for JLCPCB order
2024-05-11 Changed Blind Vias into Through holes, cut the ground layer around the vias to prevent shorting and also make it work with JLCPCB requirements (they do not make half/blind vias)
2024-05-11 Same as last commit but I actually saved the file this time
2024-05-11 Fixed IMU positioning
2024-05-17 Fixed DRC error
2024-06-03 fix imu pin position, connect SDO pin to ground, change i2c resistors from 40k to 4k
2024-06-03 add old IMU
2024-06-09 fianl PCB review before ordering
2024-06-12 fix before manufacturing: move power trace away from 12V, added member names on silkscreen
2024-06-15 ordered PCB
2024-10-14 added simple protection on motor data lines. added buttons for Jerry's button code. Removed unused parts, cleaned up schematic
2024-10-25 Started the power button files
2024-10-26 removed the power conversion unit, added step-down voltage convertor
2024-10-26 Working on stuff
2024-10-30 Latest update on the power PCB. Alternative button being used as symbol for preferred button hasn't been found yet
2024-11-01 Cleaned circuit up a little
2024-11-01 First iteration of the new board with new functions
2024-11-01 Committing the footprint libraries that were created + organized
2024-11-01 Made foorprints and PCB for button
2024-11-01 Added Arshiya's 12v to 5v buck converter
2024-11-01 Fixed XT60 polarity
2024-11-01 Fixed Drain and Source
2024-11-02 Fixed some routing
2024-11-04 Fixed PCB for new size
2024-11-04 Very rough changes for size constraint.
2024-11-23 -added label on each motor connections, -thickened 3.3v wires, removed uart line squiggles, updated U1 12v to 6v dcdc converter to new pxo7806-500
2024-11-24 Fixed PCB based on Nam's comments. Also added a button for Bootloader
2024-11-24 Verified circuit; also added button as per Nam's request
2024-11-30 Adding the footprint for the button. Also cleaned up repo (for manufacturing files). Added .gitignore
2024-11-30 Organizing a little; added .gitignore and removed Manufacturing from tracking changes
2024-12-09 changed battery side XT60 into a vertical one
2024-12-09 Adding stuff
2024-12-09 Put zener diodes back on front of the board
2024-12-09 Moved a trace away from edge
2024-12-09 Put the zener diode on front side
2024-12-09 Some extra stuff
2025-01-04 Shortened size of backup board in case we need to reorder
2025-02-01 Smaller board, changed header back to male, optimized some stuff
2025-02-11 increased motor protection diode to 6.2 V
    removed boot loader button
    added a 5pin jst connection using same i2c connection as screen Please enter the commit message for your changes. Lines starting
2025-02-11 Made some fixes
2025-02-20 updated motor protection tvs diode and kelvin sense circuit to sensing
2025-02-24 re-added the bootloader button
2025-02-24 re-added the bootloader button for jumper wire
2025-03-01 Reviewed Mike's changes of Jeff's design
2025-03-01 some parts and footprint review
2025-03-16 Added Silkscreen for version and pins
2025-09-14 initial pdb files
2025-09-20 chip layout, still need finalize a few peices and check for stock
2025-09-21 some trace done
2025-09-22 finshed all connection, need double checking datasheet and componenet availaibility on JLC
2025-09-27 init for main board
2025-09-27 init
2025-09-27 Added MCP2551 Transceiver
2025-10-25 initial board sch
2025-11-01 updated schematic and pcb; now need to add spi pins
2025-11-24 updated estop circuit and buck converters for 16 and 6 volts, groups formed for pcb layout
2025-12-11 finished componetnes placement, now need to add traces and pours
2025-12-29 finished all traces for pcb, including power and mcu sections. 1. need to look into 15V jetson power ripple (ldo) 2. pgnd and agnd seperation, star connection, 0 ohm connnection, or solder paste conn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
2026-01-03 finished solder mask removal, switched to a smaller crystal, finished osc signal isolation
2026-01-04 exposed back plate gnd trace
2026-02-01 edited master mcu section
2026-02-01 refined slave mcu section
2026-02-21 updated routing for shorter power trace
2026-04-04 competed
2026-05-23 updated vcap, reworked on power plane, added debug led and uart to 1 slave
2026-06-13 inital schematic
2026-06-26 layout
2026-06-27 schematic change
